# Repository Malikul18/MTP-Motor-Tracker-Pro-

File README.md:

# Flyer MTP
<div align="center">

  </div>
# MTP-Motor-TrackerPro-
<div align="center">
  
</div>

## Optimalisasi Operasional dengan Pelacakan Realtime dan Kesehatan Kendaraan Berbasis ESP32

MTP atau Motor Tracker Pro adalah perangkat pelacak motor canggih yang terhubung langsung dengan smartphone Anda, dirancang untuk memberikan kontrol dan pemantauan penuh terhadap kendaraan Anda. Fungsi utamanya adalah melacak lokasi motor secara real-time dan mencatat waktu setiap lokasi dikirimkan, sehingga Anda dapat memonitor pergerakan kendaraan dengan mudah.

Dengan teknologi IoT, aplikasi Motor Tracker Pro memungkinkan pengguna untuk menghidupkan motor dan mengunci starter secara cerdas melalui smartphone, memberikan kontrol penuh atas keamanan motor Anda kapan pun dibutuhkan. Selain itu, aplikasi ini menampilkan informasi lengkap tentang suhu dan kelembapan mesin, memungkinkan pengguna memantau kondisi mesin dan memastikan performa tetap optimal. Motor Tracker Pro memberikan pengalaman monitoring motor yang aman, praktis, dan terintegrasi.

## Manfaat
Motor Tracker Pro memberikan berbagai manfaat yang signifikan bagi penggunanya, terutama dalam hal keamanan dan kenyamanan. Berikut beberapa manfaat utama dari alat ini:

1. **Keamanan Motor yang Lebih Terjamin**  
   Dengan pelacakan lokasi real-time dan pemberitahuan waktu lokasi dikirim, Anda dapat memantau posisi motor kapan saja, mengurangi risiko pencurian. Fitur penguncian jarak jauh melalui aplikasi juga menambah lapisan keamanan ekstra.

2. **Pengoperasian Motor yang Lebih Mudah dan Fleksibel**  
   Fitur IoT memungkinkan Anda menghidupkan motor atau mengunci starter melalui smartphone. Manfaat ini berguna saat Anda ingin memanaskan motor dari jarak jauh atau mengunci motor dengan cepat jika terjadi hal yang mencurigakan.

3. **Pemantauan Kondisi Mesin untuk Perawatan yang Lebih Baik**  
   Informasi suhu dan kelembapan mesin yang ditampilkan di aplikasi membantu Anda memantau kondisi motor, sehingga Anda bisa mengetahui tanda-tanda awal jika ada masalah pada mesin, seperti potensi overheating atau kelembapan yang berlebihan, yang dapat memengaruhi performa.

4. **Efisiensi Waktu dan Praktis**  
   Dengan kendali motor yang ada di smartphone, Anda dapat mengakses motor kapan saja dan dari mana saja tanpa perlu berada di dekatnya. Ini sangat berguna untuk pengguna yang sering bepergian atau parkir di tempat umum.

5. **Pemantauan Rute dan Riwayat Lokasi**  
   Motor Tracker Pro membantu Anda melacak riwayat pergerakan motor, sehingga Anda dapat mengidentifikasi rute yang telah dilalui. Hal ini berguna untuk memantau penggunaan motor oleh orang lain atau mengetahui area mana yang lebih sering dilalui.

6. **Pengalaman Berkendara yang Lebih Tenang**  
   Dengan fitur keamanan dan monitoring yang lengkap, Anda dapat lebih tenang dan merasa aman saat meninggalkan motor di tempat parkir atau saat motor dipinjam oleh orang lain.

Motor Tracker Pro adalah solusi lengkap untuk pemantauan, keamanan, dan perawatan motor yang modern dan praktis, menjadikan kendaraan Anda lebih aman dan nyaman.

## Support By :
>- Dosen Pengampu : Akhmad Hendriawan ST., MT. (NIP.197501272002121003)
>- Mata kuliah : IoT dan Jaringan Sensor
>- Program Studi : D4 Teknik Elektronika
>- Politeknik Elektronika Negeri Surabaya<br>

## Team Member :
|      NRP      |       Nama      |    Jobdesk    |   Akun |
| :-----------:|:----------------:| :------------:| :-----:|
| 2122500038    | Malikul ula Al Farizi  | Project Manager       | [Malikul18] (https://github.com/Malikul18)
| 2122500041    | Tegar Bagus Aditya         |   Programmer  | [LEEEOOONNN] (https://github.com/LEEEOOONNN)
| 2122500047    | Aziza Octavia         |    UI/UX Designer      | [Azizaoct] (https://github.com/Azizaoct)
| 2122500049    | Dikri Sadam Panca Sakti                | Hardware | [DKRSDMPNCSKT] (https://github.com/DKRSDMPNCSKT)
| 2122500054    | Dwie Maulana Kalyana               | Data Analist     | [Dwiemaulana] (https://github.com/Dwiemaulana)

#Daftar Isi
- [Komponen](#Komponen)
- [Diagram Arsitektur Sistem](#Diagram-Arsitektur-Sistem)
- [Hardware](#Hardware)
- [Software](#Software)
- [Desain Prototype](#Desain-Prototype)
   * [Desain UI/UX MTP](#Desain-UI/UX-MTP)
- [Rincian Biaya](#Rincian-Biaya)

# Komponen
1. ESP32
2. Relay 2 Channel
3. Sensor GPS Neo-6M
4. RTC
5. DHT22
6. Module Step-Down

# Diagram Arsitektur Sistem
<div align="center">

  </div>
  
## Cara Kerja Motor Tracker Pro Secara Singkat**  
1. Pelacakan Lokasi Real-Time  
   - Perangkat ini dilengkapi modul GPS (seperti ublox NEO-6M) yang mendeteksi lokasi motor.  
   - Informasi lokasi dikirim ke Broker HiveMQ lalu dilanjutkan ke Kodular 
   - Data ini ditampilkan di aplikasi smartphone Anda dalam bentuk peta, sehingga Anda bisa memantau posisi motor kapan saja.  

2. Kontrol Motor via Smartphone  
   - Perangkat terhubung ke sistem starter motor melalui modul IoT.  
   - Dengan aplikasi, Anda bisa mengirim perintah untuk menghidupkan motor atau mengunci starter.  
   - Perintah dikirim melalui jaringan internet ke perangkat di motor, lalu dieksekusi secara otomatis.  

3. Pemantauan Suhu dan Kelembapan Mesin  
   - Sensor suhu dan kelembapan di perangkat membaca kondisi mesin motor.  
   - Data ini dikirimkan ke aplikasi, membantu Anda memantau performa mesin dan mendeteksi potensi masalah lebih awal.  

4. Riwayat Lokasi dan Pemberitahuan  
   - Sistem mencatat setiap lokasi yang dilalui motor dan menyimpannya di server.  
   - Anda bisa melihat riwayat pergerakan motor dan mendapatkan notifikasi saat motor berpindah tempat.  

5. Keamanan Tambahan  
   - Jika motor terdeteksi bergerak tanpa izin, Anda bisa segera mengunci starter melalui aplikasi.  
   - Lokasi motor yang terus dilacak memudahkan Anda menemukan kendaraan jika hilang.  

Hasilnya, dengan Motor Tracker Pro, Anda mendapatkan kontrol penuh dan real-time terhadap motor, baik untuk keamanan, kenyamanan, maupun perawatan mesin.
  
# Youtube MTP 
- Vidio iklan [Motor Tracker Pro](https://youtube.com/shorts/t2EillxIgAg?feature=share)
- Vidio Presentasi Part 1 [Presentasi MTP 1](https://youtu.be/_fa9HbBBqg8?si=ezKUigorlg2BFhqz)
- Vidio Presentasi Part 2 [Presentasi MTP 2](https://youtu.be/dOQvoxRiuMA?si=DrRlcXq3RNPgVKTd)
- Vidio Pengujian Komponen DS18B20 [Pengujian Komponen DS18B20](https://youtu.be/Lpr0joNosio)
- Vidio Pengujian Relay [Pengujian Relay](https://youtu.be/rNnlRDHxlcc)

# Hardware
## Prototype MTP
<div align="center">

</div>
<div align="center">

</div>

## Layout PCB MTP
<div align="center">

</div>

## Schematic PCB MTP
<div align="center">

</div>

## Board PCB Layer Atas dan Bawah
<div align="center">

</div>

# Software
## Pengujian Relay 2 Channel sebagai Kunci dan Starter Sepeda Motor
Program ini menggunakan *ESP32* untuk mengontrol dua relay melalui aplikasi *Blynk*. Relay adalah komponen elektronik yang berfungsi seperti saklar, yang bisa dikendalikan secara elektronik. Pada Projek ini Kontrol relay digunakan untuk menyalakan dan mematikan kunci dan starte sepeda motor menggunakan smartphone sebagai inovasi IoT dari salah satu fungsui MTP.Cara kerja program :
1. ESP32 terhubung ke Wi-Fi dan aplikasi Blynk.
2. Di aplikasi Blynk, pengguna mengontrol dua tombol virtual (V0 dan V1):
   - Tombol V0 mengontrol relay di pin 2.
   - Tombol V1 mengontrol relay di pin 15.
3. Saat tombol ditekan, relay menyala (membuka sirkuit).
4. Saat tombol dilepas, relay mati (menutup sirkuit).
5. Status relay dikembalikan ke aplikasi Blynk dan ditampilkan di Serial Monitor.

#define BLYNK_TEMPLATE_ID "TMPL6gpzdGcuz"
#define BLYNK_TEMPLATE_NAME "Kunci Relay"
#define BLYNK_AUTH_TOKEN "fu98OTmzLjvvY9Xmn6revk_N22ejEKPd"

#include <WiFi.h>
#include <WiFiClient.h>
#include <BlynkSimpleEsp32.h>

BlynkTimer timer;
#define relay 2
#define relay1 15
int SW_relay = 0;
int SW1_relay = 0;

char auth[] = "fu98OTmzLjvvY9Xmn6revk_N22ejEKPd";
const char* ssid = "--NamaSsidPerangkat--";
const char* pass = "--PassWiFi--";

void setup() {
  Serial.begin(9600);
  pinMode(relay, OUTPUT);
  pinMode(relay1, OUTPUT);
  Blynk.begin(auth, ssid, pass);
  Serial.println(("ESP32 - Relay MTP_Simulation"));
  Serial.println();
}

 void loop() {
  Blynk.run();
  timer.run();
}

BLYNK_WRITE(V0)
{
  SW_relay = param.asInt();
  if (SW_relay == 1){
    digitalWrite(relay, HIGH);
    Serial.println("Relay terbuka");
    Blynk.virtualWrite(V0, HIGH);
  }else{
    digitalWrite(relay, LOW);
    Serial.println("Relay tertutup");
    Blynk.virtualWrite(V0, LOW);
  }
}
BLYNK_WRITE(V1)
{
  SW1_relay = param.asInt();
  if (SW1_relay == 1){
    digitalWrite(relay1, HIGH);
    Serial.println("Relay1 terbuka");
    Blynk.virtualWrite(V1, HIGH);
  }else{
    digitalWrite(relay1, LOW);
    Serial.println("Relay1 tertutup");
    Blynk.virtualWrite(V1, LOW);
  }
}

## Pengujian Sensor DS18B20 untuk Memantau Suhu Mesin Sepeda Motor
Program ini adalah implementasi *IoT* menggunakan ESP32 untuk membaca suhu mesin sepeda motor dari sensor *DS18B20* dan mengirimkan serta menampilkan datanya ke aplikasi *Blynk*. Cara Kerja Program :
1. ESP32 terhubung ke Wi-Fi dan aplikasi Blynk.
2. DS18B20 membaca suhu secara berkala (setiap 1 detik).
3. Suhu yang terbaca:
   - Ditampilkan di *Serial Monitor* untuk debugging.
   - Dikirim ke aplikasi Blynk melalui *Virtual Pin V0*.
4. Di aplikasi Blynk, suhu dapat dimonitor secara real-time.

#define BLYNK_TEMPLATE_ID "TMPL6WFMyxSwG"
#define BLYNK_TEMPLATE_NAME "DS18B20Temperature"
#define BLYNK_AUTH_TOKEN "M0G-asq9c1-Qyj-I_5InTObtkUO7urGc"

#include <WiFi.h>
#include <WiFiClient.h>
#include <BlynkSimpleEsp32.h>
#include <OneWire.h>
#include <DallasTemperature.h>

const int dataPin = 2;// Pin yang terhubung ke pin DATA DS18B20

OneWire oneWire(dataPin);// Membuat instance dari OneWire
DallasTemperature sensors(&oneWire);// Membuat instance dari DallasTemperature

BlynkTimer timer;

char auth[] = "M0G-asq9c1-Qyj-I_5InTObtkUO7urGc";
const char* ssid = "--NamaSsidPerangkat--";
const char* pass = "--PassWiFI--";

void setup() {
  Blynk.begin(auth, ssid, pass);
  // Memulai komunikasi serial
  Serial.begin(9600);

  // Memulai sensor DS18B20
  sensors.begin();
}

void loop() {
  // Meminta sensor untuk melakukan pembacaan suhu
  sensors.requestTemperatures();

  // Membaca suhu dalam Celsius dari sensor pertama (index 0)
  float temperatureC = sensors.getTempCByIndex(0);

  // Menampilkan suhu di Serial Monitor
  Serial.print("Suhu: ");
  Serial.print(temperatureC);
  Serial.println(" °C");
  Blynk.virtualWrite(V0, temperatureC);

  delay(1000); // Membaca suhu setiap 1 detik
  Blynk.run();
  timer.run();
}

# Desain Prototype
## Desain UI/UX MTP
Tampilan awal UI/UX MTP      |   
 | | 
 | 
- [Figma](https://www.figma.com/design/K79DKEpYAUl1oy9ZEVzn8G/Prototyping-in-Figma?node-id=0-1&node-type=canvas&t=O9agAbHADH6BsXUb-0)
- Prototype *MTP* menggunakan Figma untuk UI/UX adalah sebuah desain antarmuka interaktif yang bertujuan untuk memvisualisasikan konsep dan alur pengguna dari sebuah aplikasi atau sistem yang sedang dikembangkan. Prototipe ini memungkinkan pengguna atau pemangku kepentingan untuk memahami bagaimana aplikasi akan berfungsi, termasuk navigasi, tata letak, dan interaksi antar elemen di dalamnya. Dalam Figma, prototipe *MTP* dapat mencakup elemen-elemen seperti tombol, form input, menu, serta transisi antar halaman atau skenario pengguna.
## Kodular 
Untuk realisasi dari protoype menggunakan kodular 
<src = "Program/MTP_tracking_GPS.aia">

# Link Wokwi
(https://wokwi.com/projects/411652017077715969)

# Rincian Biaya
| No  | Item                   | Jumlah | Harga   | Total   |
|-----|------------------------|--------|---------|---------|
| 1   | ESP32 Devkitc 32D      | 1      | 66.900  | 66.900  |
| 2   | 2 Channel Relay Module 5V/3.3V    | 1     | 15.000   | 15.000   |
| 3   | GPS Module Ublox NEO 6M V2          | 1      | 74.500     | 74.500     |
| 4   | Tinny RTC DS1307          | 1      | 10.000  | 10.000  |
| 5   | DHT22 Module Sensor      | 1      | 70.000     | 70.000     |
| 6   | Project Board Power Module      | 1      | 12.000   | 12.000   |
| 7   | 3D Print Casing        | -      | -  | -  |
|     |                        |        |         |         |

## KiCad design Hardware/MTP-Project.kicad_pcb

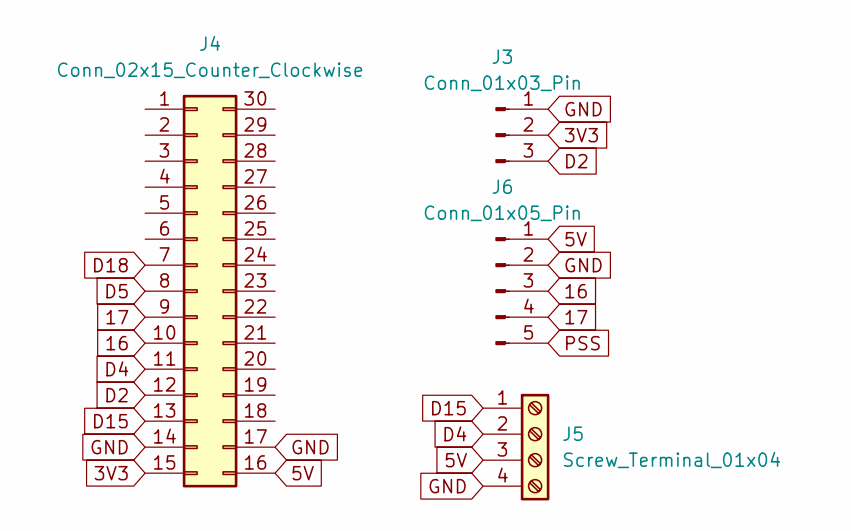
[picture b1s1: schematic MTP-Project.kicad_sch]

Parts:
J3: Conn_01x03_Pin; PinSocket_1x03_P2.54mm_Vertical
J4: Conn_02x15_Counter_Clockwise; ESP_Test
J5: Screw_Terminal_01x04; TerminalBlock_MetzConnect_Type175_RT02704HBLC_1x04_P7.50mm_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
J6: Conn_01x05_Pin; PinSocket_1x05_P2.54mm_Horizontal

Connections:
3V3: J3.2, J4.15
5V: J4.16, J5.3, J6.1
16: J4.10, J6.3
17: J4.9, J6.4
D2: J3.3, J4.12
D4: J4.11, J5.2
D5: J4.8
D15: J4.13, J5.1
D18: J4.7
GND: J3.1, J4.14, J4.17, J5.4, J6.2
PSS: J6.5

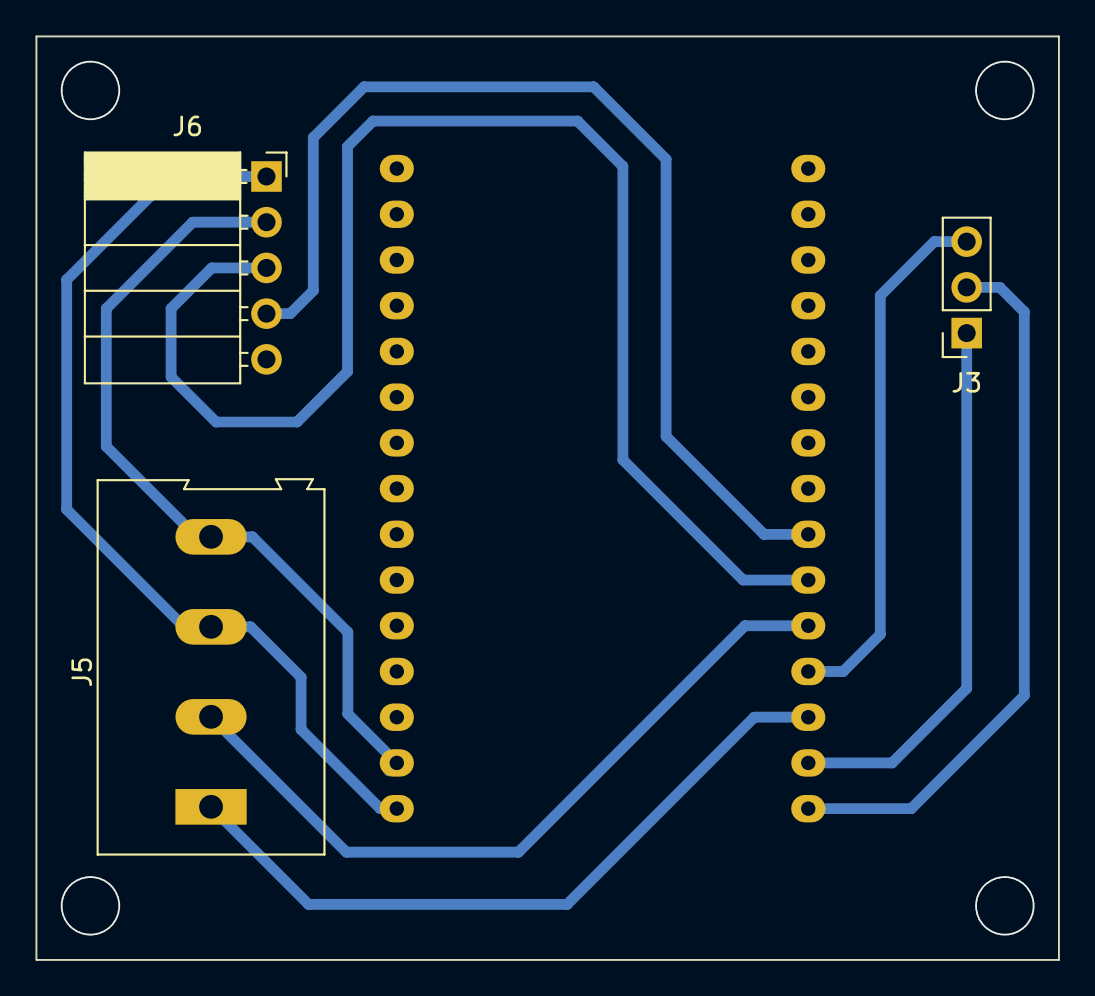
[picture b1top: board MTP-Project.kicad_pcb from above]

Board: 2 copper layers, 56.8 x 51.3 mm, 4 parts (0 on the bottom side), 8 nets.

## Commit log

2024-10-13 Create Assets
2024-10-13 Create Prototype
2024-10-13 Menambahkan link desain UI/UX Figma Prototype
2024-10-21 Program integrasi ESP32 dengan modul GPS
2024-10-21 integrasi ESP32 dengan modul GPS
2024-11-04 RELAY_2CH.ino
2024-11-07 Add files via upload
    Berikut merupakan wiring dari rangkaian pengujian komponen Relay, GPS module, dan DHT22
2024-11-10 Update flyer
2024-11-21 Add files via upload
    broker MQTT + sensor integrated done
2024-11-25 Add files via upload
    berikut merupakan rangkian schematic dan layout pcb dari MTP
2024-11-25 Add files via upload
    Berikut merupakan schematic pcb dan diagram blok dari sistem MTP
